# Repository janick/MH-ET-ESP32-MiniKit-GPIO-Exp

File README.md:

# GPIO Expander for MH-ET ESP32 MiniKit with On-Board A/C Supply

I'm not a board designer, so this is probably very naive, but it works for building ESPHome-based sensors
and other small IoT projects.

All the GPIOs on the "inner" rows are routed to the terminals, so there is no need to solder all
of the pins on the MiniKit all the time.
The (optional) NPN transistor (and 10k resistor) can be used to sink an external
LED that mirrors the on-board LED but that requires that GPIO2 be soldered through as it sits on
one of the "outer" rows.

Get bare boards directly from OSHPark: https://oshpark.com/shared_projects/CoKjk6w7

## Parts

* ESP-32 MiniKit: https://www.aliexpress.com/item/2251832629758482.html
* Power Supply: https://www.aliexpress.com/item/2251832424359134.html
* MiniKit Shields: https://www.aliexpress.com/item/2251832856833499.html
* Screw Terminals: https://www.aliexpress.com/item/3256802913222907.html

## Stupid Mistakes

* IO20 labels on the underside should be "IO23".
* All 6 pins in a row in the prototyping array are connected together. I should have done 3+3 so an IC could be used.
* Make the 5V and A/C traces wider
* Add protection to the power supply (https://forum.mysensors.org/topic/1607/safe-in-wall-ac-to-dc-transformers)

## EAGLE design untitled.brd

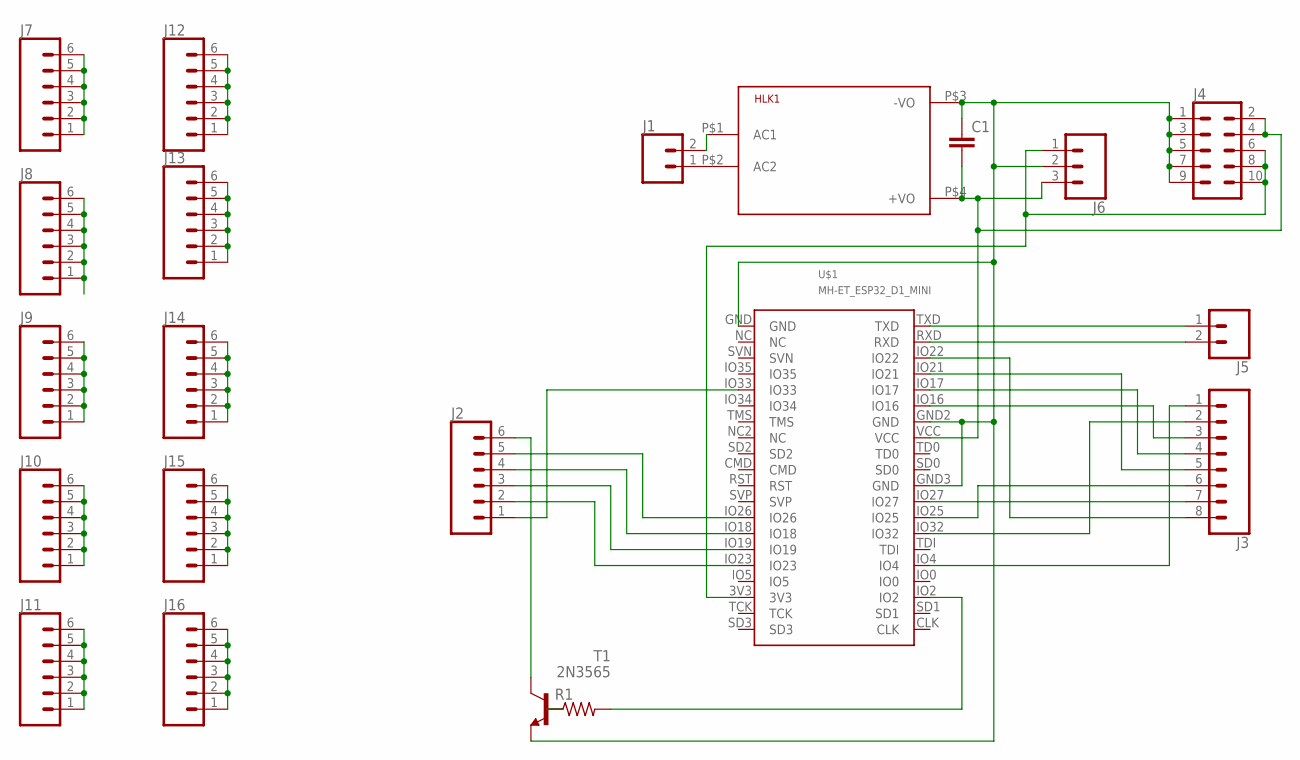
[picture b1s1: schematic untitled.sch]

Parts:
C1: C2.5/2; C2.5-2
HLK1: HLK-PM013W; HLK-PM01
J1: CONN_023.5MM; SCREWTERMINAL-3.5MM-2
J2: CONN_063.5MM-6; SCREWTERMINAL-3.5MM-6
J3: CONN_083.5MM-8; SCREWTERMINAL-3.5MM-8
J4: CONN_05X2NO_SILK; 2X5_NOSILK
J5: CONN_02; 1X02
J6: CONN_03SCREW; SCREWTERMINAL-3.5MM-3
J7, J8, J9, J10, J11, J12, J13, J14, J15, J16: CONN_06SILK_FEMALE_PTH; 1X06
R1: R-US_0204/5; 0204/5
T1: 2N3565; TO92
U$1: MH-ET_ESP32_D1_MINI

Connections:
GND: C1.1, HLK1.P$3 (-VO), J4.1, J4.3, J4.5, J4.7, J4.9, J6.2, T1.3 (E), U$1.GND, U$1.GND2 (GND), U$1.GND3 (GND)
unnamed: HLK1.P$2 (AC2), J1.1
unnamed: R1.1, T1.2 (B)
unnamed: J2.6, T1.1 (C)
unnamed: J2.5, U$1.IO26
unnamed: J2.4, U$1.IO18
unnamed: J2.3, U$1.IO19
unnamed: J2.2, U$1.IO23
unnamed: J2.1, U$1.IO33
unnamed: HLK1.P$1 (AC1), J1.2
unnamed: C1.2, HLK1.P$4 (+VO), J4.2, J4.4, J6.3, U$1.VCC
unnamed: J5.1, U$1.TXD
unnamed: J5.2, U$1.RXD
unnamed: J4.6, J4.8, J4.10, J6.1, U$1.3V3
unnamed: R1.2, U$1.IO2
unnamed: J3.8, U$1.IO22
unnamed: J3.6, U$1.IO25
unnamed: J3.3, U$1.IO16
unnamed: J3.4, U$1.IO17
unnamed: J3.7, U$1.IO27
unnamed: J3.5, U$1.IO21
unnamed: J3.1, U$1.IO4
unnamed: J3.2, U$1.IO32
unnamed: J7.1, J7.2, J7.3, J7.4, J7.5, J7.6
unnamed: J8.1, J8.2, J8.3, J8.4, J8.5, J8.6
unnamed: J9.1, J9.2, J9.3, J9.4, J9.5, J9.6
unnamed: J10.1, J10.2, J10.3, J10.4, J10.5, J10.6
unnamed: J11.1, J11.2, J11.3, J11.4, J11.5, J11.6
unnamed: J12.1, J12.2, J12.3, J12.4, J12.5, J12.6
unnamed: J13.1, J13.2, J13.3, J13.4, J13.5, J13.6
unnamed: J14.1, J14.2, J14.3, J14.4, J14.5, J14.6
unnamed: J15.1, J15.2, J15.3, J15.4, J15.5, J15.6
unnamed: J16.1, J16.2, J16.3, J16.4, J16.5, J16.6

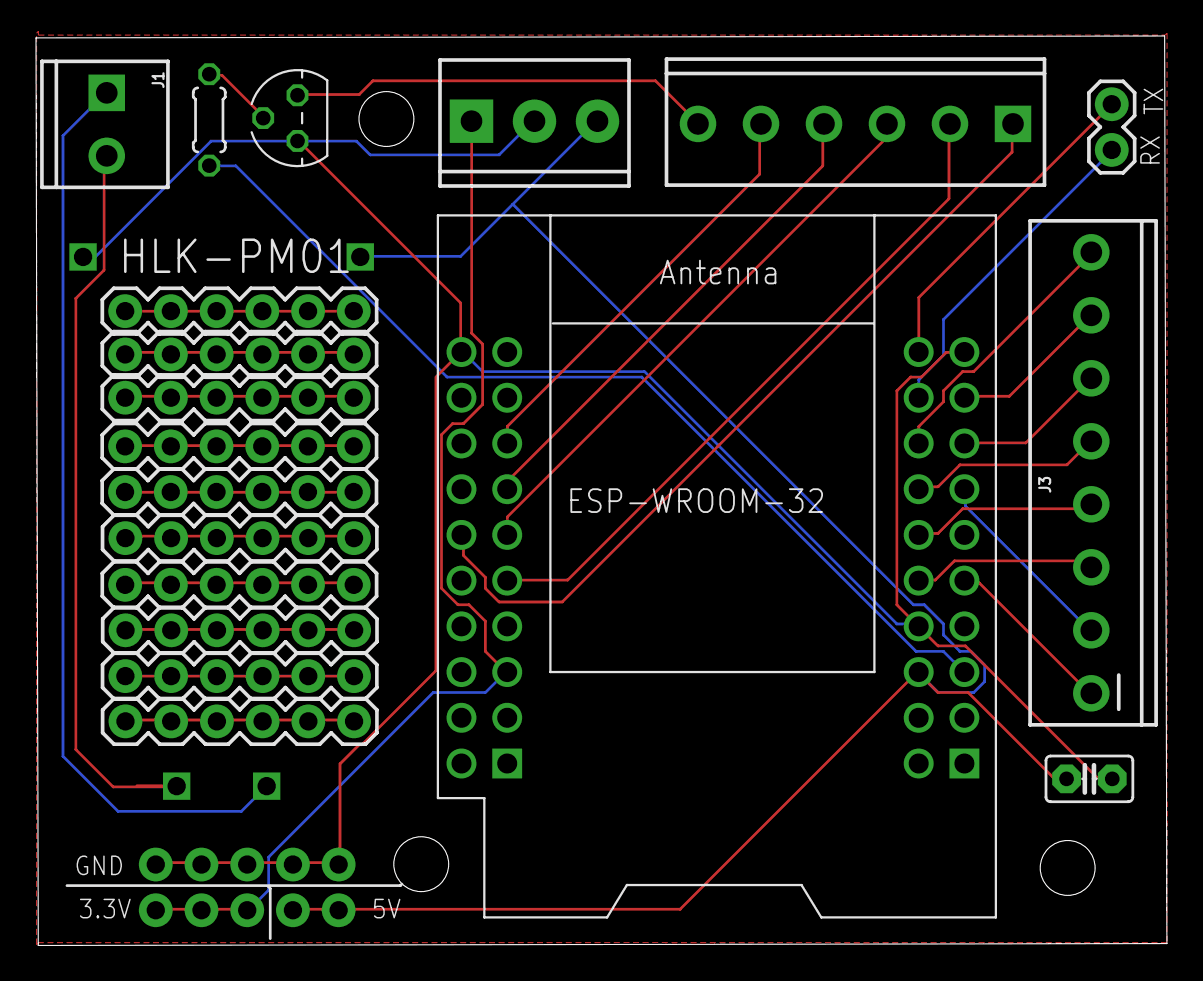
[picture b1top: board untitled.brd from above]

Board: 2 copper layers, 62.8 x 50.5 mm, 21 parts (0 on the bottom side), 33 nets.

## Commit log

2022-06-24 Initial upload
2022-06-24 Add photo of boards
2022-06-24 Added part list
2022-06-24 "Shield", not "Cape"
2022-06-24 Point to screw terminals with correct pitch
2022-06-25 Added details on which pins on the MiniKit needs to be soldered through.
2022-06-25 NPN is optional
2022-06-25 One stupid mistake noted.
2022-06-26 A couple more stupid mistakes
2022-07-03 Woops. IO20 shoudl be IO23

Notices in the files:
parts and their libraries:
SparkFun-Connectors: Licensing: Creative Commons ShareAlike 4.0 International - https://creativecommons.org/licenses/by-sa/4.0
